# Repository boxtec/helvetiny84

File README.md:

# helvetiny84
HelveTiny84

here you can find the Board Helvetiny84. A small Attiny84 bases Development Board, 
with a direct USB Implementation Micronucleus.

If you would like to buy our kit: https://shop.boxtec.ch/helvetiny84-kit-p-42861.html

Documentation: https://playground.boxtec.ch/doku.php/arduino/attinyusb/helvetiny84

Tutorials: https://playground.boxtec.ch/doku.php/arduino/attinyusb/helvetiny84/tutorials

Support Thread: https://forum.boxtec.ch/index.php/topic,3162.0.html

If you would like to have a smaller board check the helvetiny85: https://github.com/boxtec/helvetiny85

Have fun.
Dinoi

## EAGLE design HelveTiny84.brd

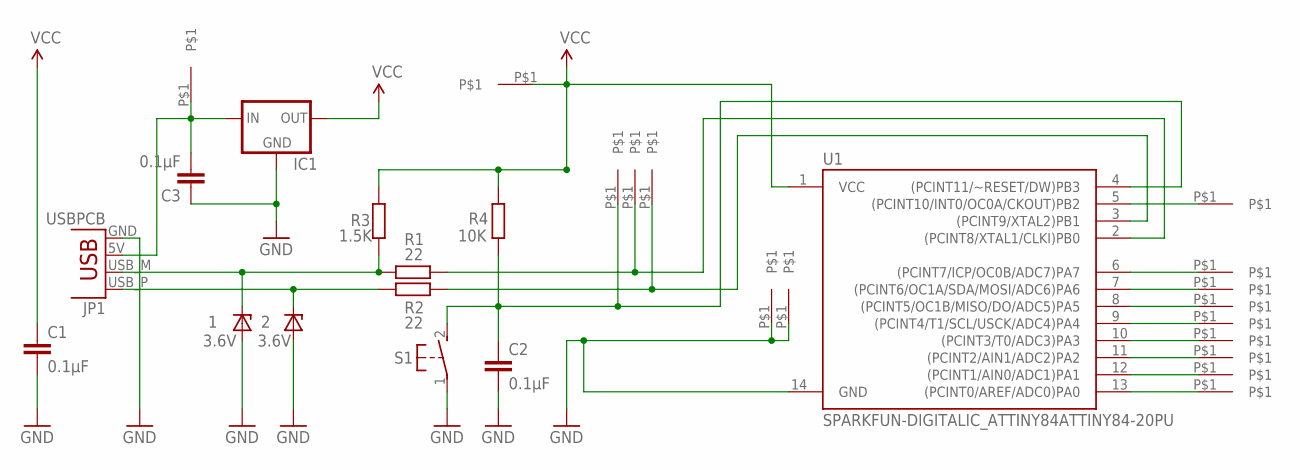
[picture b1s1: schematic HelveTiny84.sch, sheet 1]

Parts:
1, 2: 3.6V; ZDIO-7.5
C1, C2, C3: 0.1μF; C025-024X044
D3, D4, D5, D6, D7, D8: FLOWERPIN
IC1: MCP1700TRI; TO92
JP1: USBPCB; USB-A-PCB
R1, R2: 22; 0207/7
R3: 1.5K; 0207/7
R4: 10K; 0207/7
S1: S3; DTS-3
TP1, TP2, TP29, TP30, TP31, TP32, TP33, TP34, TP35, TP36: FLOWERPIN
U1: SPARKFUN-DIGITALIC_ATTINY84ATTINY84-20PU; SPARKFUN-DIGITALIC_DIL14

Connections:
D0: TP33.P$1, U1.13 ((PCINT0/AREF/ADC0)PA0)
D1: TP34.P$1, U1.12 ((PCINT1/AIN0/ADC1)PA1)
D2: TP35.P$1, U1.11 ((PCINT2/AIN1/ADC2)PA2)
GND: 1.A, 2.A, C1.2, C2.2, C3.1, IC1.1 (GND), JP1.GND, S1.1, TP2.P$1, TP32.P$1, U1.14 (GND)
unnamed: D7.P$1, U1.6 ((PCINT7/ICP/OC0B/ADC7)PA7)
unnamed: D6.P$1, U1.7 ((PCINT6/OC1A/SDA/MOSI/ADC6)PA6)
unnamed: D5.P$1, U1.8 ((PCINT5/OC1B/MISO/DO/ADC5)PA5)
unnamed: D4.P$1, U1.9 ((PCINT4/T1/SCL/USCK/ADC4)PA4)
unnamed: D3.P$1, U1.10 ((PCINT3/T0/ADC3)PA3)
unnamed: D8.P$1, U1.5 ((PCINT10/INT0/OC0A/CKOUT)PB2)
RESET: C2.1, R4.1, S1.2, TP29.P$1, U1.4 ((PCINT11/~RESET/DW)PB3)
USB-IN-M: 1.C, JP1.USB_M (D-), R1.1, R3.1
USB-IN-P: 2.C, JP1.USB_P (D+), R2.1
USB-M: R1.2, TP30.P$1, U1.2 ((PCINT8/XTAL1/CLKI)PB0)
USB-P: R2.2, TP31.P$1, U1.3 ((PCINT9/XTAL2)PB1)
VCC: C1.1, IC1.3 (OUT), R3.2, R4.2, TP36.P$1, U1.1 (VCC)
VIN: C3.2, IC1.2 (IN), JP1.5V (VBUS), TP1.P$1

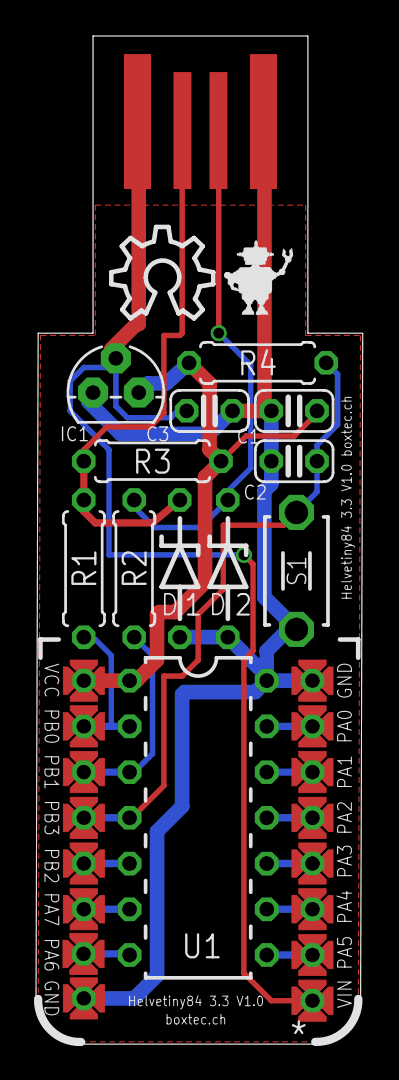
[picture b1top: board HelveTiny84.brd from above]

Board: 2 copper layers, 18.2 x 56.0 mm, 30 parts (0 on the bottom side), 17 nets.

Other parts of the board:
U$1: OSHW_10X200_NOTEXT

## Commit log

2017-10-06 Helvetiny84 Fritzing Part

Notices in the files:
parts and their libraries:
SparkFun-Connectors: Licensing: Creative Commons ShareAlike 4.0 International - https://creativecommons.org/licenses/by-sa/4.0
